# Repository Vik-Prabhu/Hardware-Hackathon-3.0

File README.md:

# 1. Title of the project
**Green Node**

# 2. Problem Statement
The global agricultural sector faces a massive adoption gap in precision agriculture. Out of over 500 million small farms globally, only about 10% use digital agricultural services.
- **Prohibitive Costs**: Commercial sensor nodes cost upwards of $200–$250 per unit, with traditional cellular IoT incurring high recurring costs and requiring expensive trenching.
- **Hardware Failures**: Many existing solutions fail in harsh agricultural environments, suffering from battery death during cold snaps or UV degradation.
- **Sensor Inaccuracies**: Low-cost sensors claim to measure nutrients but actually measure soil electrical conductivity, leading to high inaccuracies.
- **Data Fatigue**: Farmers are overwhelmed with raw data rather than actionable insights.
- **Yield vs. Money Disconnect**: Agritech often visualizes agronomy but fails to show economic impact.

# 3. Objective
To build a low-cost, scalable, and open-source plantation monitoring system for the Hardware Hackathon 3.0. Green Node merges robust hardware edge nodes with a sophisticated AI advisory pipeline to bring state-of-the-art agricultural monitoring to farmers. Our core objective focuses on plant survival, optimal yield, and early disease prevention through high-accuracy local ground truth.

# 4. Existing work
The current market is split between expensive agricultural tech and software-heavy platforms lacking local ground truth:
| Competitor | Approach | Weakness |
|---|---|---|
| **Fasal** | Farm-specific IoT | Very high hardware cost, vertical-specific |
| **CropIn** | Software-only platform | No on-ground sensors (estimations only) |
| **Manual Contractors**| Schedule-based inspection | Inefficient, unaccountable |

# 5. Gap analysis
Despite the rise of precision agriculture, competitors fail due to **scaling constraints and disconnected methodologies**. Existing systems lack integration between cheap continuous ambient measurement and deep-learning visual diagnostics. Solutions like Fasal capture field data but demand massive capital ($200+ unit cost), while CropIn relies purely on estimates without true real-world soil/plant mapping. 

Green Node bridges this gap by decoupling continuous soil telemetry from computationally heavy vision tasks—delivering a comprehensive package for under ₹2,400 per node, combined with actionable, real-time AI-guided triaging devoid of monthly LTE service drops.

# 6. Novelty
The core novelty resides in our **Dual-Node Architecture linked to an AI Advisory Pipeline**:
Instead of providing raw datasets like "humidity is 78%", Green Node features a visual capture layer. The camera node feeds leaf images into an AI model combined with live ambient data. The system generates intelligent, multi-lingual daily action priorities—e.g., *"Node 3 has early signs of Late Blight — inspect row 4."*
Additionally, we leverage **Dynamic Sentinal Polling**: Sensor nodes dynamically change their reporting frequency based on internal thresholds (e.g. accelerating ping rates from 30s to 5s during severe moisture drops).

# 7. Your project description
Green Node is a fully integrated ecosystem designed to deliver actionable intelligence. It incorporates:
1. **Hardware Edge Nodes:** Custom-designed PCB routing, deploying ESP32-C3 for continuous environmental tracking (temperature, humidity, moisture, light) and ESP32-CAM nodes for visual plant health assessments.
2. **Comprehensive Data Backend:** Built with FastAPI and an SQLite embedded database to handle data ingestion over local Wi-Fi without internet cellular reliance.
3. **AI Health Advisory Pipeline:** Contextually combined sensor data and visual image scans generate daily Action Plans translated into Tamil, Telugu, Kannada, Hindi, and Bengali using Sarvam AI, complete with audio TTS capabilities.
4. **Earthy Editorial Dashboard:** A fully responsive bespoke dashboard providing clear, animated, high-end insights for the modern facility or farmer.

# 8. List of components and the software used
### Hardware Components
* **MCU:** ESP32-C3 Dev Module (RISC-V) & AI-Thinker ESP32-CAM (ESP32-S).
* **Sensors:** DHT11 / DHT22 (Temperature & Humidity), Capacitive Soil Moisture Sensor v1.2, GL5528 LDR (Ambient Light), OV2640 (2MP Camera).
* **Power:** 5V/3.3V custom regulating PCB headers.

### Software Stack
* **Microcontroller Firmware:** C++ (Arduino Framework), `DHT sensor library`, `ArduinoJson`.
* **Backend Core:** Python (FastAPI, Uvicorn, APScheduler), SQLite.
* **Frontend Design:** Vue.js / VitePress / HTML interfaces.
* **Microservices:** Gemini Vision models natively proxied through a Sarvam AI API pipeline for multilingual translation and audio rendering.

# 9. Methodology
To validate our system in a real-world edge scenario, we deployed it in a live indoor bonsai nursery:
- **Node N-01 (Camera + Env Node):** Captured on-demand 800×600 SVGA SVGA imagery alongside DHT22 inputs whenever the server requested.
- **Node N-02 (Soil Node):** Pushed telemetry continuously every 30 seconds via HTTP POST, adjusting frequency whenever threshold rules were broken.
Data is sent explicitly through local WiFi `mDNS` structures routing directly to a secure, localized central Python Hub—acting as a firewall from public internet threats.

# 10. Work flow
1. **Boot Sequence:** Both nodes power up, synchronize UTC timing via NTP, and POST their IPs to `vikram-Vivobook-Go.local:8000/register`. 
2. **Measurement Cycle (Continuous):** The Soil Node (N-02) wakes, tracks variables, and evaluates internal thresholds to set loop delays (5s vs 30s) before executing an HTTP POST with JSON data.
3. **Capture Cycle (Pull):** The central server queries the Vision Node (N-01) at `GET /capture`. The node streams a JPEG byte packet alongside `X-Moisture` and `X-Temperature` custom headers.
4. **AI Inference & Translation:** The local Hub fuses the image and historical sensor values, passing it to an AI proxy. Sarvam AI retrieves the analysis, translating the diagnostic into local languages.
5. **Dashboard Reflection:** The end-user operates the Vue dashboard reading the localized `Daily Action Plan`.

# 11. Pic of the project/ prototype

# 12. Demo video
*[Insert Link to Live Project Demo Video Here]*

# 13. Create a public github repo and attach the following
*The current repository encompasses the complete documentation, firmware, server environment, and backend code designed explicitly according to the 13-point rubric constraints.*
**Repository URL**: [https://github.com/Vik-Prabhu/Hardware-Hackathon-3.0](https://github.com/Vik-Prabhu/Hardware-Hackathon-3.0)

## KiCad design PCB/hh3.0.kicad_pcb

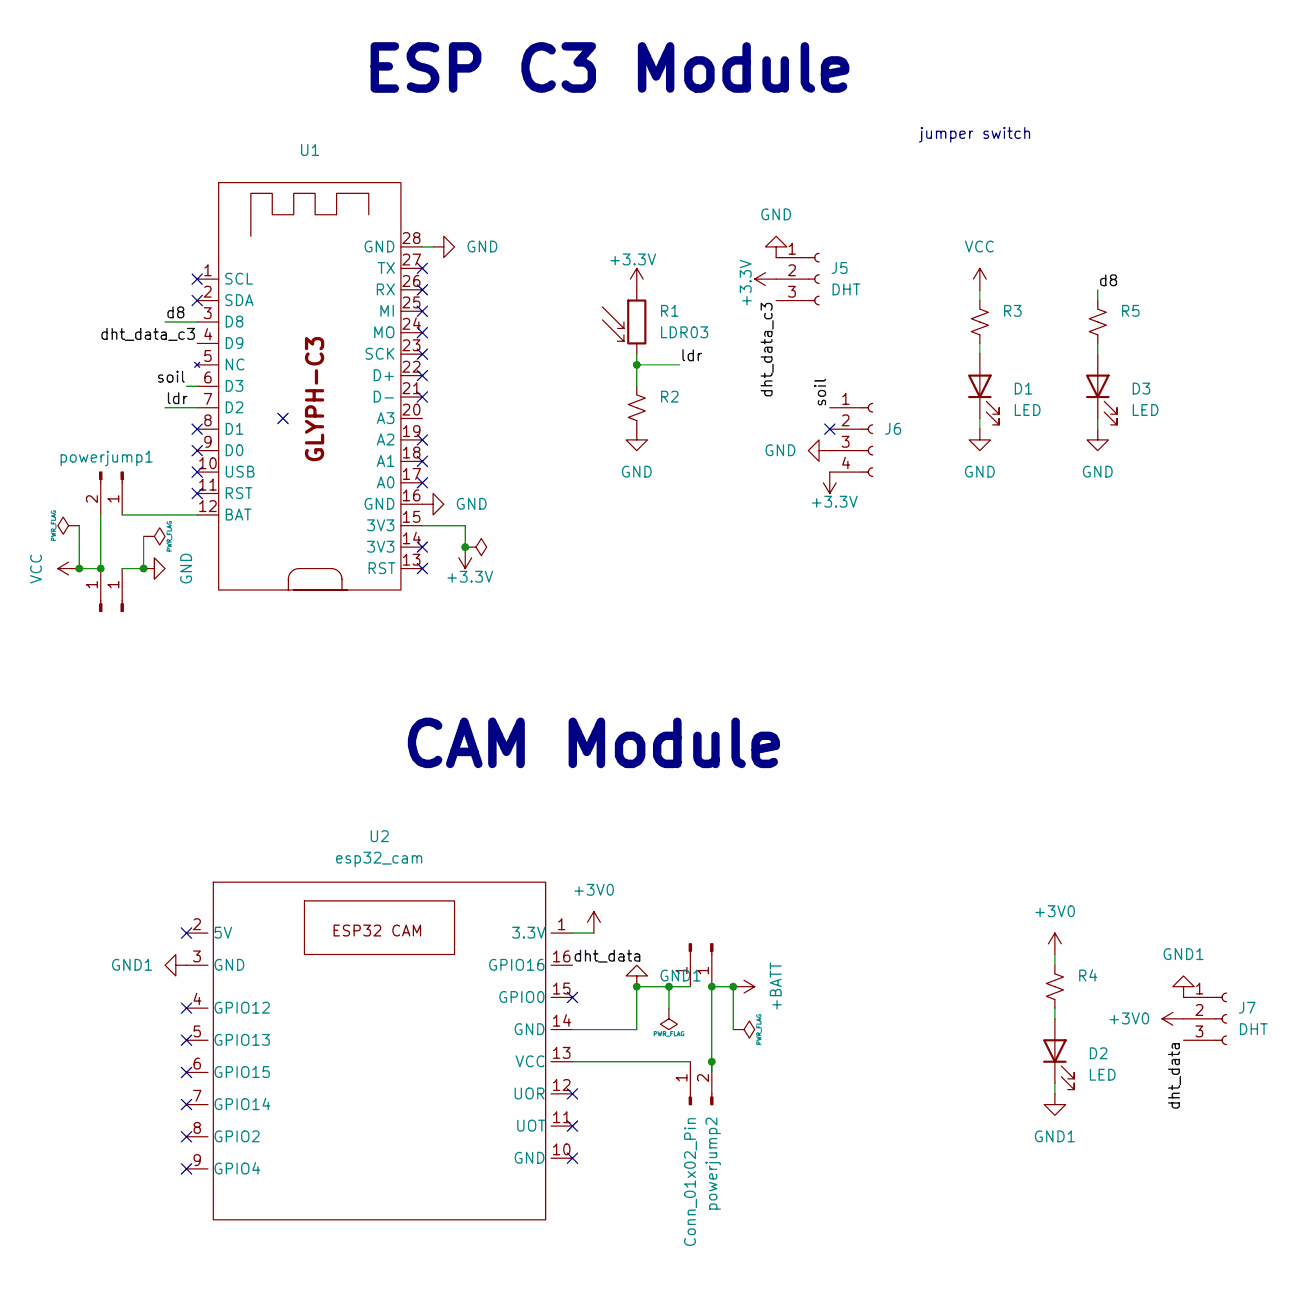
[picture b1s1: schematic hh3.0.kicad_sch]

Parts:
D1, D2, D3: LED; LED_D3.0mm_Clear
J1, J2, J3, J4: Conn_01x01_Pin; SolderWirePad_1x01_SMD_1x2mm
J5, J7: DHT; PinSocket_1x03_P2.54mm_Vertical
J6: Conn_01x04_Socket; PinHeader_1x04_P2.54mm_Vertical
R1: LDR03; R_LDR_4.9x4.2mm_P2.54mm_Vertical
R2: 100k; R_Axial_DIN0204_L3.6mm_D1.6mm_P5.08mm_Horizontal
R3, R4, R5: R_Small_US; R_Axial_DIN0204_L3.6mm_D1.6mm_P5.08mm_Horizontal
U1: glyph-c3
U2: esp32_cam
powerjump1, powerjump2: Conn_01x02_Pin; PinHeader_1x02_P2.54mm_Vertical

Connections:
+3.3V: J5.2, J6.4, R1.1, U1.15 (3V3)
+3V0: J7.2, R4.1, U2.1 (3.3V)
+BATT: J4.1, powerjump2.2
/d8: R5.1, U1.3 (D8)
/dht_data: J7.3, U2.16 (GPIO16)
/dht_data_c3: J5.3, U1.4 (D9)
/ldr: R1.2, R2.1, U1.7 (D2)
/soil: J6.1, U1.6 (D3)
GND: D1.1 (K), D3.1 (K), J2.1, J5.1, J6.3, R2.2, U1.16 (GND), U1.28 (GND)
GND1: D2.1 (K), J3.1, J7.1, U2.3 (GND), U2.14 (GND)
unnamed: D1.2 (A), R3.2
unnamed: D2.2 (A), R4.2
unnamed: D3.2 (A), R5.2
unnamed: U1.12 (BAT), powerjump1.1
unnamed: U2.13 (VCC), powerjump2.1
VCC: J1.1, R3.1, powerjump1.2

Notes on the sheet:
jumper switch
CAM Module
ESP C3 Module

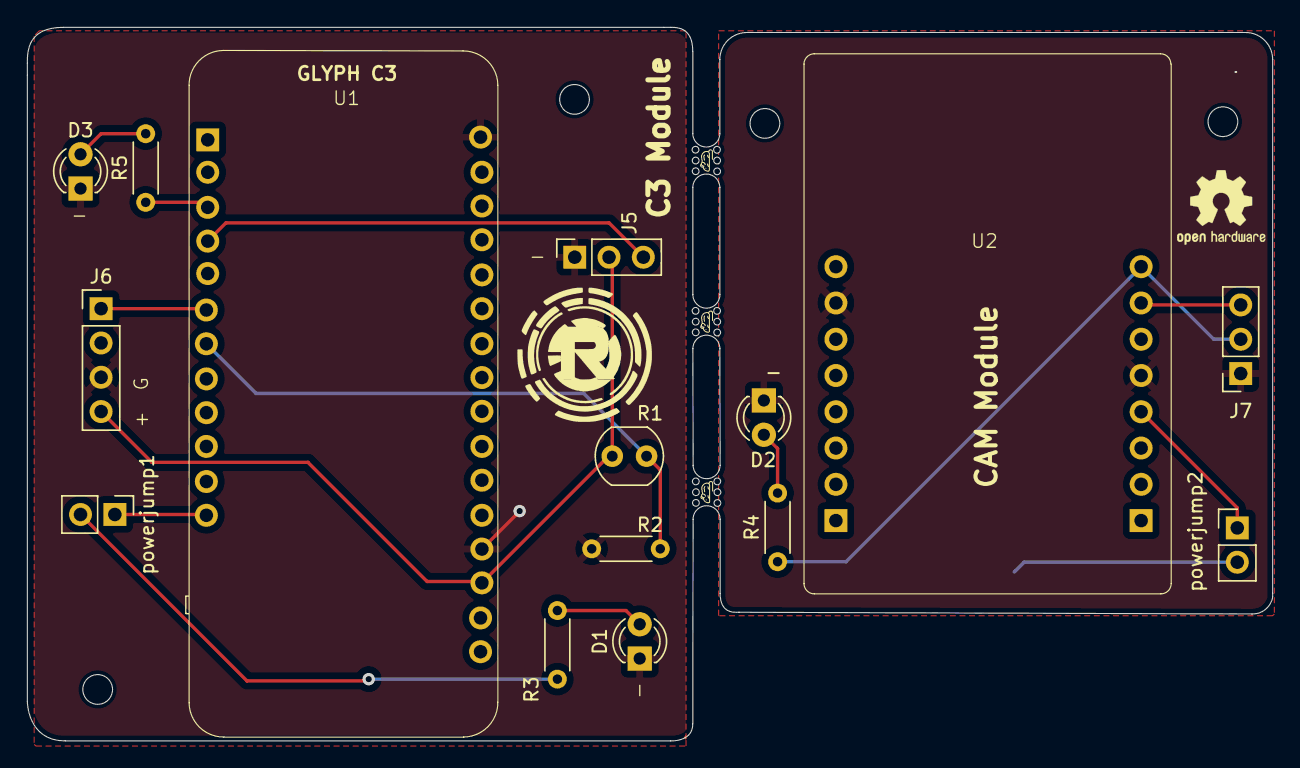
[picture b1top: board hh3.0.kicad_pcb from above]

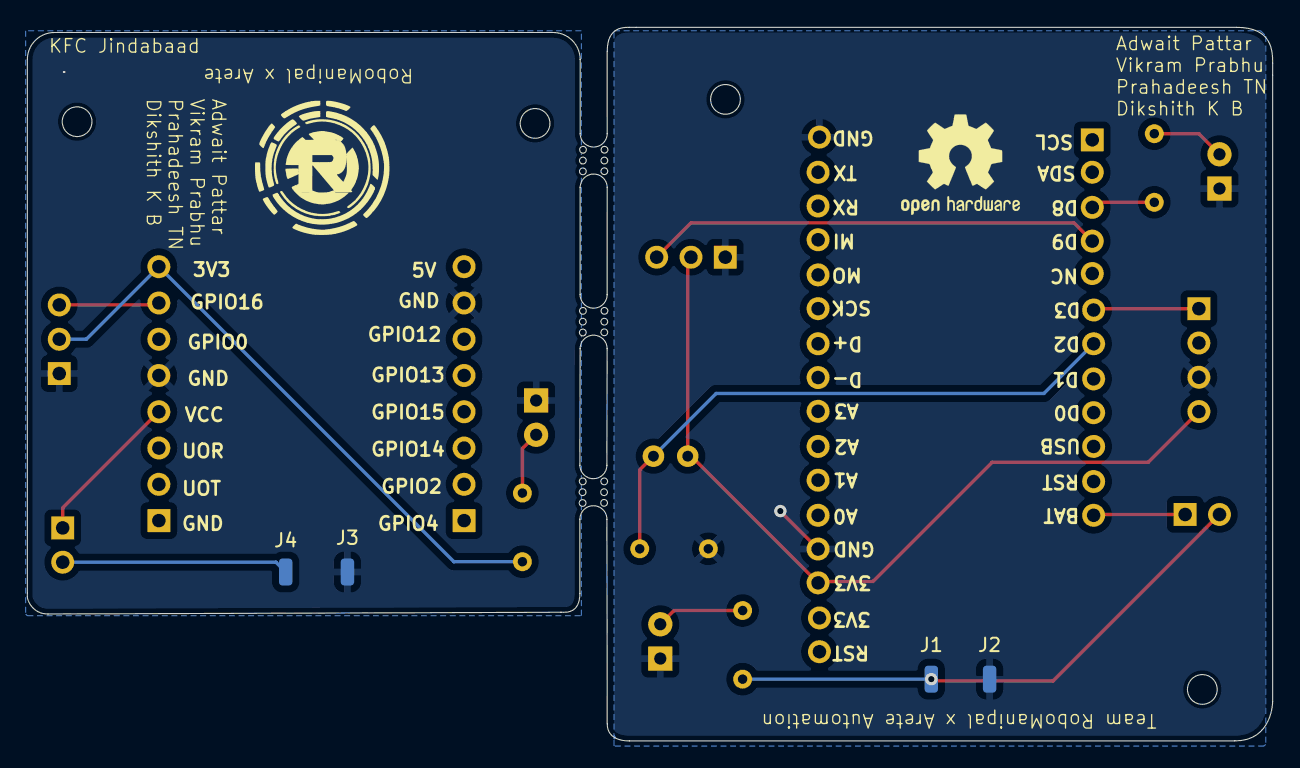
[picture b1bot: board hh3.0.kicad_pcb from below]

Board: 2 copper layers, 92.2 x 52.8 mm, 22 parts (4 on the bottom side), 16 nets.

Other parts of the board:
mouse-bite-2mm-4mm, mouse-bite-2mm-4mm#2, mouse-bite-2mm-4mm#3: VAL**; mouse-bite-2mm-4mm

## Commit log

2026-04-10 inital commit
2026-04-10 added market research
2026-04-10 dashboardv1
2026-04-10 dashboardv2
2026-04-10 dashboardv3
2026-04-11 added gitignore
2026-04-11 basic functionality working
2026-04-11 added firmware
2026-04-11 added glyphc3 firmware
2026-04-11 local ai partially integrated
2026-04-11 ai integrated
2026-04-12 added daily plan feature
2026-04-12 partial documenation
2026-04-12 documentation v1
2026-04-12 minor fixes
2026-04-12 updated gitignore
2026-04-12 added PCB and Minor webpage fixes
2026-04-14 final commit
